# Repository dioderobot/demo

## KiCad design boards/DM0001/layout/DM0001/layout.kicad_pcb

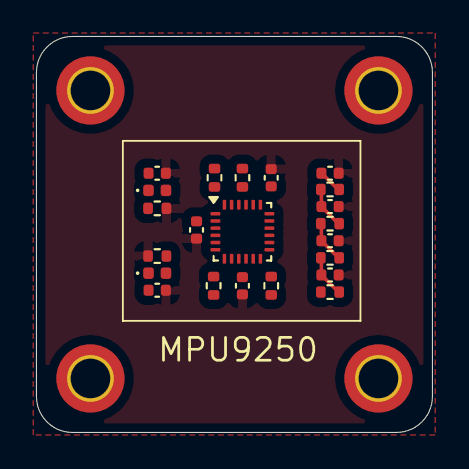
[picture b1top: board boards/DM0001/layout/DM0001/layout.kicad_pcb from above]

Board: 4 copper layers, 22.0 x 22.0 mm, 26 parts (0 on the bottom side), 13 nets.

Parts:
C1, C2, C3, C9: 100nF; C_0402_1005Metric
C4, C5, C6, C7, C8: 10nF; C_0402_1005Metric
D1, D2: LED GREEN; LED_0402_1005Metric
H1, H2, H3, H4: M2 DIN965 TopBottom; MountingHole_2.2mm_M2_DIN965_Pad_TopBottom
R1, R10: 1k; R_0402_1005Metric
R2, R3: 4.7k; R_0402_1005Metric
R4, R5: 10k; R_0402_1005Metric
R6, R7, R8, R9: 820; R_0402_1005Metric
U1: ?; InvenSense_QFN-24_3x3mm_P0.4mm

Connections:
Imu.LED.L: D1.1, R1.1
Imu.MPU9250.CS_PULLUP: R4.1, U1.22
Imu.MPU9250.REGOUT: C2.1, U1.10
Imu.NC: R3.1, U1.21
Imu.NC_2: R2.1, U1.7
LowPassFilter.STAGE1_OUT: C5.1, R6.2, R7.1
LowPassFilter.STAGE2_OUT: C6.1, R7.2, R8.1
LowPassFilter.STAGE3_OUT: C7.1, R8.2, R9.1
MCU_IN: C8.1, R9.2
PowerLed.L: D2.1, R10.1
SENSOR_OUT: R5.1, R6.1, U1.12
gnd_GND: C1.2, C2.2, C3.2, C4.2, C5.2, C6.2, C7.2, C8.2, C9.2, R1.2, R10.2, U1.9, U1.18, U1.20
vcc_VCC: C1.1, C3.1, C4.1, C9.1, D1.2, D2.2, R2.2, R3.2, R4.2, R5.2, U1.1, U1.8, U1.13

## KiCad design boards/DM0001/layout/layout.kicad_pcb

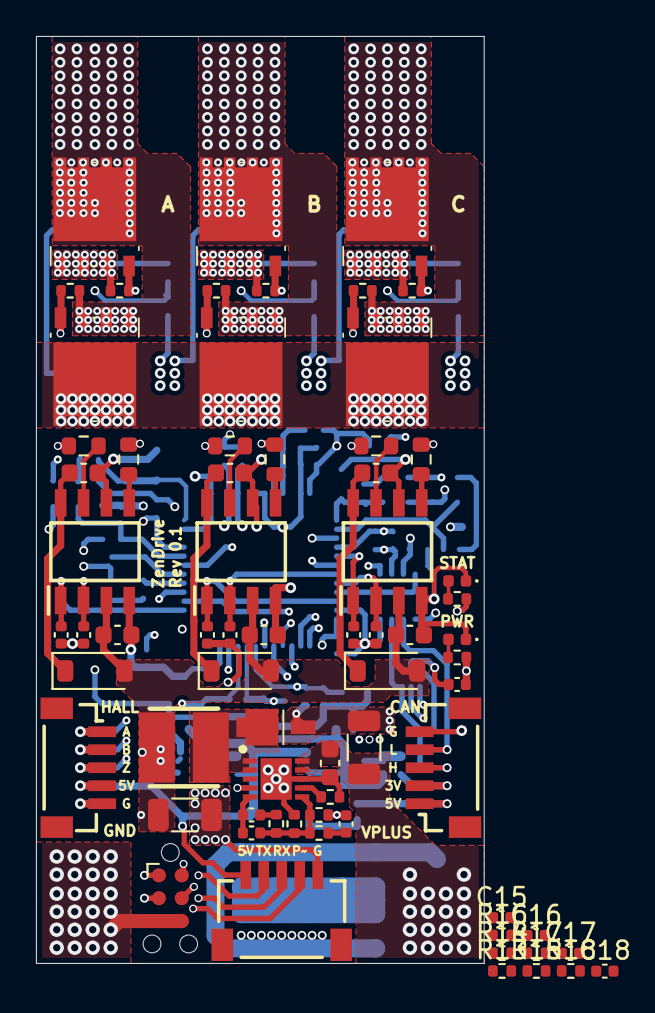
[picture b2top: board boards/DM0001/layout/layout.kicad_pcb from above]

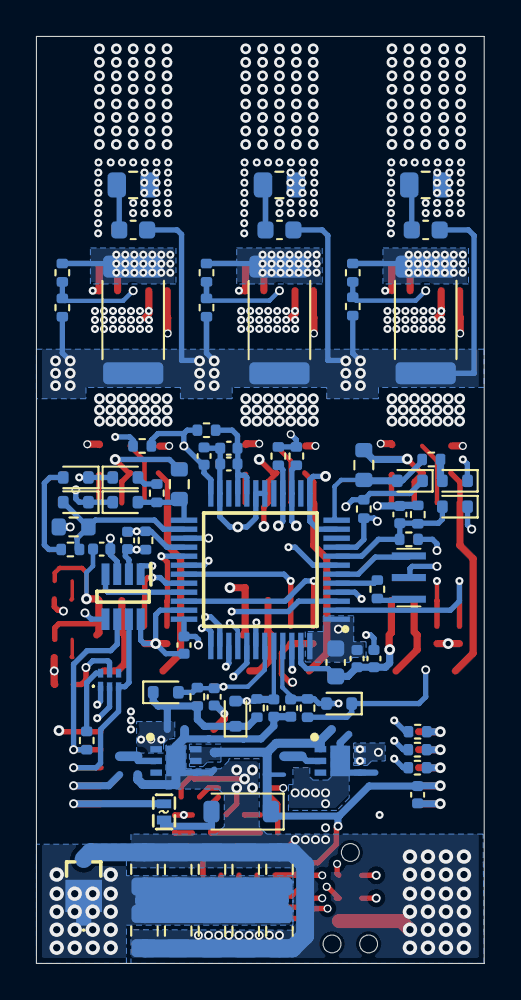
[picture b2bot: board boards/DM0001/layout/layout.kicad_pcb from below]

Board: 6 copper layers, 24.9 x 51.5 mm, 149 parts (80 on the bottom side), 85 nets.

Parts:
C1: CL31B106KAHNNNE; C_1206_3216Metric
C2: GCM188R71H224KA64D; C_0603_1608Metric
C3: CL31A226MOCLNNC; C_1206_3216Metric
C4: GCM1555C1H300FA16D; C_0402_1005Metric
C5: GRM155R71H472KA01D; C_0402_1005Metric
C6: CL05B392KB5NNNC; C_0402_1005Metric
C7: CL05B103KB5NNNC; C_0402_1005Metric
C8, C9, C10, C14, C44, C45, C47, C50: GCM155R71H104KE02D; C_0402_1005Metric
C11, C12, C13: GCM1555C1H100FA16D; C_0402_1005Metric
C15, C17: 1uF 10% 25V; C_0402_1005Metric
C16, C18: 2.2uF 10% 16V; C_0402_1005Metric
C19, C24, C29: GRM1885C1H102JA01D; C_0603_1608Metric
C20, C25, C30: GCM188R71E105KA64D; C_0603_1608Metric
C21, C22, C26, C27, C31, C32: GCM1555C1H101FA16D; C_0402_1005Metric
C23, C28, C33: CL10A474KA8NNNC; C_0603_1608Metric
C34, C35, C36, C37, C38, C39, C40, C41, C42, C43: C2012X5R1V226M125AC; C_0805_2012Metric
C46: GRM188Z71C475KE21D; C_0603_1608Metric
C48: CL05A105KP5NNNC; C_0402_1005Metric
C49: GRM1555CYA103GE01D; C_0402_1005Metric
D1: STPS1L40M
D2: 1N5817W; D_SOD-123
D3, D4, D5, D6, D7, D8, D10, D11, D13, D14: BAT30KFILM; D_SOD-523
D9, D12, D15: STPS0560Z; D_SOD-123
D16: VLMG1500-GS08; LED_0402_1005Metric
D17: VLMS1500-GS08; LED_0402_1005Metric
F1: 0435.250KRS; F0402
FB1: MMZ1005S601CT000; R_0402_1005Metric
IC1: TCAN330DCNT; SOT65P280X145-8N
IC2, IC3: LDFPVR; SON65P200X200X100-7N-D
IC4, IC5, IC6: L6387ED; SOIC127P600X175-8N
IC7: STM32G431C8T6; QFP50P900X900X160-48N
J1, J2: BM05B-SRSS-TB(LF)(SN); BM05BSRSSTB
J3: SM05B-SRSS-TB(LF)(SN); SM05BSRSSTB
J4: ?; Tag-Connect_TC2030-IDC-NL_2x03_P1.27mm_Vertical
L1: ?; IND-SMD_L3.9-W3.9
PS1: L7986TR; SON50P300X300X100-11N-D
Q1, Q2, Q3, Q4, Q5, Q6: STL180N6F7; STL140N6F7
R1, R45: ERJ-2RKF4701X; R_0402_1005Metric
R2: ERJ-2RKF3000X; R_0402_1005Metric
R3: ERJ-2RKF3482X; R_0402_1005Metric
R4: ERJ-2RKF8201X; R_0402_1005Metric
R5: ERJ-2RKF62R0X; R_0402_1005Metric
R6: ERJ-2RKF1200X; R_0402_1005Metric
R7, R8, R9, R10, R11, R12, R13, R16, R21, R23, R29, R31, R37, R39: ERJ-2RKF1002X; R_0402_1005Metric
R14: ERJ-2RKF3092X; R_0402_1005Metric
R15, R18: ERJ-2RKF4702X; R_0402_1005Metric
R17: ERJ-2RKF5232X; R_0402_1005Metric
R19, R27, R35, R49, R50, R51: ERJ-2RKF2201X; R_0402_1005Metric
R20, R22, R28, R30, R36, R38: ERJ-3EKF33R0V; R_0603_1608Metric
R24, R32, R40: ERJ-3EKF1002V; R_0603_1608Metric
R25, R33, R41: RC0805JR-071RL; R_0805_2012Metric
R26, R34, R42: CSNL2512FT3L00; R_2512_6332Metric
R43, R44: ERJ-2RKF1001X; R_0402_1005Metric
R46: ERJ-2RKF1802X; R_0402_1005Metric
R47: ERJ-2RKF1693X; R_0402_1005Metric
R48: ERJ-2RKF2200X; R_0402_1005Metric
R52, R53, R54: ERJ-2RKF2202X; R_0402_1005Metric
R55, R56, R57: ERJ-2RKF1501X; R_0402_1005Metric
S1: FSA5157L6X
TH1: NTCG103JF103FT1; R_0402_1005Metric
Y1: CSTNE8M00GH5C000R0; CSTNE12M0GH5L000R0
Z1: SMM4F26A-TR; SMM4F15ATR

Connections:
A_PLUS_H1: C11.1, D4.2, IC7.43, R7.2, R8.2
BEMF1: D8.2, IC7.12, R19.2, R24.2
BEMF2: D11.2, IC7.26, R27.2, R32.2
BEMF3: D14.2, IC7.25, R35.2, R40.2
B_PLUS_H2: C12.1, D5.2, IC7.44, R9.2, R10.2
Buck.COMP: C4.1, C5.2, PS1.5
Buck.FB: C4.2, PS1.6, R1.2, R2.1, R4.1, R5.2
Buck.FSW: PS1.7, R3.1
Buck.OUT: D1.1, D1.2, L1.1, PS1.1, PS1.2
Buck.R_SMALL_SIGNAL: C5.1, R4.2
Buck.R_SMALL_SIGNAL_2: C6.2, R5.1
CAN_RX: IC1.4, IC7.33
CAN_SHDN: IC1.5, IC7.27
CAN_TERM: IC7.3, S1.1
CAN_TX: IC1.1, IC7.46
CURR_FDBK1_OPAMP+: IC7.9, R49.1, R52.2, R55.1
CURR_FDBK2_OPAMP+: IC7.15, R50.1, R53.2, R56.1
CURR_FDBK3_OPAMP+: IC7.16, R51.1, R54.2, R57.1
Can_Interface.CAN_H: IC1.7, J1.3, S1.3
Can_Interface.CAN_L: IC1.6, J1.4, R6.1
Can_Interface.FUSE: D2.2, F1.1
Can_Interface.JST_5V: F1.2, J1.1
Can_Interface.S1: R6.2, S1.6
GND: C1.2, C2.2, C3.2, C7.2, C8.2, C9.2, C10.2, C11.2, C12.2, C13.2, C14.2, C15.2, C16.2, C17.2, C18.2, C19.2, C21.2, C22.2, C23.2, C24.2, C26.2, C27.2, C28.2, C29.2, C31.2, C32.2, C33.2, C34.2, C35.2, C36.2, C37.2, C38.2, C39.2, C40.2, C41.2, C42.2, C43.2, C44.2, C45.2, C46.2, C47.2, C48.2, C49.2, C50.2, D1.3, D16.1, D17.1, IC1.2, IC1.8, IC2.4, IC2.7, IC3.4, IC3.7, IC4.4, IC5.4, IC6.4, IC7.11, IC7.13, IC7.18, IC7.19, IC7.23, IC7.35, IC7.47, J1.5, J2.5, J3.5, J4.5, J4.6, PS1.8, PS1.11, R2.2, R3.2, R13.2, R16.2, R26.2, R34.2, R42.2, R45.2, R46.2, R49.2, R50.2, R51.2, S1.5, Y1.2, Z1.2
GPIO_BEMF: D7.1, D10.1, D13.1, IC7.42
HallEncoder.A_PLUS_H1_IN: J2.1, R8.1
HallEncoder.B_PLUS_H2_IN: J2.2, R10.1
HallEncoder.Z_PLUS_H3_IN: J2.3, R12.1
Ldo_3V3.LDFPVR.NC_LDFPVR_PG: IC2.3, R15.1
Ldo_3V3._ADJ: IC2.2, R13.1, R14.2
Ldo_5V.LDFPVR.NC_LDFPVR_PG: IC3.3, R18.1
Ldo_5V._ADJ: IC3.2, R16.1, R17.2
NRST: C50.1, IC7.7, J4.3
PHASE_A: C20.2, IC4.6, Q1.1, Q1.2, Q1.3, Q2.5, Q2.6, Q2.7, Q2.8, Q2.9, R21.2, R24.1, R25.1
PHASE_B: C25.2, IC5.6, Q3.1, Q3.2, Q3.3, Q4.5, Q4.6, Q4.7, Q4.8, Q4.9, R29.2, R32.1, R33.1
PHASE_C: C30.2, IC6.6, Q5.1, Q5.2, Q5.3, Q6.5, Q6.6, Q6.7, Q6.8, Q6.9, R37.2, R40.1, R41.1
PWM: IC7.39, J3.4
PhaseDriverA.D_BEMF: D7.2, R19.1
PhaseDriverA.HI_GATE: Q1.4, R20.2, R21.1
PhaseDriverA.HVG: IC4.7, R20.1
PhaseDriverA.LO_GATE: Q2.4, R22.2, R23.1
PhaseDriverA.LVG: IC4.5, R22.1
PhaseDriverA.RC_NODE: C19.1, R25.2
PhaseDriverA.U1.BOOT: C20.1, D9.1, IC4.8
PhaseDriverB.D_BEMF: D10.2, R27.1
PhaseDriverB.HI_GATE: Q3.4, R28.2, R29.1
PhaseDriverB.HVG: IC5.7, R28.1
PhaseDriverB.LO_GATE: Q4.4, R30.2, R31.1
PhaseDriverB.LVG: IC5.5, R30.1
PhaseDriverB.RC_NODE: C24.1, R33.2
PhaseDriverB.U1.BOOT: C25.1, D12.1, IC5.8
PhaseDriverC.D_BEMF: D13.2, R35.1
PhaseDriverC.HI_GATE: Q5.4, R36.2, R37.1
PhaseDriverC.HVG: IC6.7, R36.1
PhaseDriverC.LO_GATE: Q6.4, R38.2, R39.1
PhaseDriverC.LVG: IC6.5, R38.1
PhaseDriverC.RC_NODE: C29.1, R41.2
PhaseDriverC.U1.BOOT: C30.1, D15.1, IC6.8
R_POWER_LED: D16.2, R43.2
R_STATUS_LED: D17.2, R44.2
STATUS: IC7.4, R44.1
STM32G431C8T6.R_XIN: IC7.5, R48.2
STM32G431C8T6.VDDA: C48.1, C49.1, FB1.2, IC7.20, IC7.21
STM32G431C8T6.XIN: R48.1, Y1.1
STM32G431C8T6.XOUT: IC7.6, Y1.3
SWD_SWCLK: IC7.38, J4.4
SWD_SWDIO: IC7.37, J4.2
TEMP_FEEDBACK: C7.1, IC7.28, R45.1, TH1.2
TIM1_CH1: C21.1, IC4.2, IC7.30
TIM1_CH1N: C22.1, IC4.1, IC7.2
TIM1_CH2: C26.1, IC5.2, IC7.31
TIM1_CH2N: C27.1, IC5.1, IC7.34
TIM1_CH3: C31.1, IC6.2, IC7.32
TIM1_CH3N: C32.1, IC6.1, IC7.29
UART2_RX: IC7.41, J3.3
UART2_TX: IC7.40, J3.2
V3V3: C9.1, C10.1, C16.1, C44.1, C45.1, C46.1, C47.1, D3.1, D4.1, D5.1, D6.1, D8.1, D11.1, D14.1, FB1.1, IC1.3, IC2.1, IC7.1, IC7.24, IC7.36, IC7.48, J1.2, J4.1, R7.1, R9.1, R11.1, R14.1, R43.1, R52.1, R53.1, R54.1, S1.2, TH1.1
V5V: C14.1, C15.1, C18.1, D2.1, IC2.5, IC2.6, IC3.1, J2.4, J3.1, R15.2, R17.1
V10V: C3.1, C6.1, C17.1, C23.1, C28.1, C33.1, D9.2, D12.2, D15.2, IC3.5, IC3.6, IC4.3, IC5.3, IC6.3, L1.2, R1.1, R18.2
VBUS: C8.1, D3.2, IC7.8, R46.1, R47.2
VPLUS: C1.1, C2.1, C34.1, C35.1, C36.1, C37.1, C38.1, C39.1, C40.1, C41.1, C42.1, C43.1, PS1.4, PS1.9, PS1.10, Q1.5, Q1.6, Q1.7, Q1.8, Q1.9, Q3.5, Q3.6, Q3.7, Q3.8, Q3.9, Q5.5, Q5.6, Q5.7, Q5.8, Q5.9, R47.1, Z1.1, Z1.3
VSHUNTP_A: Q2.1, Q2.2, Q2.3, R23.2, R26.1, R55.2
VSHUNTP_B: Q4.1, Q4.2, Q4.3, R31.2, R34.1, R56.2
VSHUNTP_C: Q6.1, Q6.2, Q6.3, R39.2, R42.1, R57.2
Z_PLUS_H3: C13.1, D6.2, IC7.45, R11.2, R12.2

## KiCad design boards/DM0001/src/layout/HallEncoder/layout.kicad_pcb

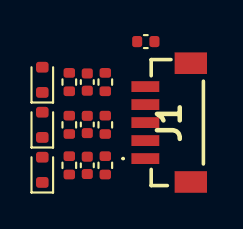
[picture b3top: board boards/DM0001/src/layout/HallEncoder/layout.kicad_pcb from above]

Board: 2 copper layers, 14 parts (0 on the bottom side), 9 nets, no tracks yet.

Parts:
C1, C2, C3: GCM1555C1H100FA16D; C_0402_1005Metric
C4: GCM155R71H104KE02D; C_0402_1005Metric
D1, D2, D3: BAT30KFILM; D_SOD-523
J1: BM05B-SRSS-TB(LF)(SN); BM05BSRSSTB
R1, R2, R3, R4, R5, R6: ERJ-2RKF1002X; R_0402_1005Metric

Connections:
A_PLUS_H1_IN: J1.1, R2.1
A_PLUS_H1_OUT: C1.1, D1.2, R1.2, R2.2
B_PLUS_H2_IN: J1.2, R4.1
B_PLUS_H2_OUT: C2.1, D2.2, R3.2, R4.2
GND: C1.2, C2.2, C3.2, C4.2, J1.5
V3V3: D1.1, D2.1, D3.1, R1.1, R3.1, R5.1
V5V: C4.1, J1.4
Z_PLUS_H3_IN: J1.3, R6.1
Z_PLUS_H3_OUT: C3.1, D3.2, R5.2, R6.2

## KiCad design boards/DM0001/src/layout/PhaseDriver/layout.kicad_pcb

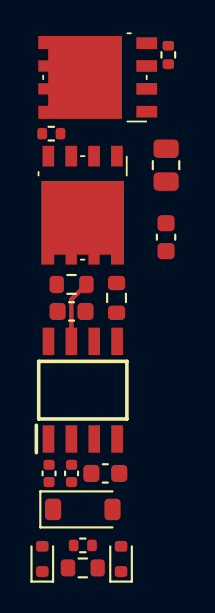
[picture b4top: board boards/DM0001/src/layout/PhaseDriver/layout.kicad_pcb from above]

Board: 2 copper layers, 19 parts (1 on the bottom side), 15 nets.

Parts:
C1: 1nF 100V; C_0603_1608Metric
C2: 1uF 25V; C_0603_1608Metric
C3, C4: 100pF 10V; C_0402_1005Metric
C5: 470nF 16V; C_0603_1608Metric
D1, D2: BAT30KFILM; D_SOD-523
D3: STPS0560Z; D_SOD-123
R1: 2.2k; R_0402_1005Metric
R2, R4: 33; R_0603_1608Metric
R3, R5: 10k; R_0402_1005Metric
R6: 10k; R_0603_1608Metric
R7: 1; R_0805_2012Metric
R8: 3m 1%; R_2512_6332Metric
U1, U2: STL180N6F7; STL140N6F7
U3: L6387ED; SOIC127P600X175-8N

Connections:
BEMF: D2.2, R1.2, R6.2
D_BEMF: D1.2, R1.1
GND: C1.2, C3.2, C4.2, C5.2, R8.2, U3.4
HI_GATE: R2.2, R3.1, U1.4
HVG: R2.1, U3.7
LO_GATE: R4.2, R5.1, U2.4
LVG: R4.1, U3.5
PHASEOUT: C2.2, R3.2, R6.1, R7.1, U1.1, U1.2, U1.3, U2.5, U2.6, U2.7, U2.8, U2.9, U3.6
RC_NODE: C1.1, R7.2
TIM_CHN: C4.1, U3.1
TIM_CHP: C3.1, U3.2
U1.BOOT: C2.1, D3.1, U3.8
VCC: C5.1, D3.2, U3.3
VPLUS: U1.5, U1.6, U1.7, U1.8, U1.9
VSHUNTP: R5.2, R8.1, U2.1, U2.2, U2.3

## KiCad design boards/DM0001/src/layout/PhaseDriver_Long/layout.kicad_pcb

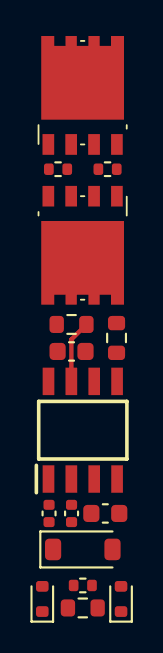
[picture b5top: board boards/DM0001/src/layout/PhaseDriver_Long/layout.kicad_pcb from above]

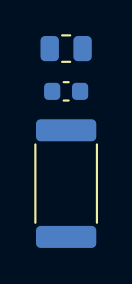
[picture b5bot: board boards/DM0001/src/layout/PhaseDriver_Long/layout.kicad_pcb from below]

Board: 2 copper layers, 19 parts (3 on the bottom side), 15 nets.

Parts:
C1: GRM1885C1H102JA01D; C_0603_1608Metric
C2: GCM188R71E105KA64D; C_0603_1608Metric
C3, C4: GCM1555C1H101FA16D; C_0402_1005Metric
C5: CL10A474KA8NNNC; C_0603_1608Metric
D1, D2: BAT30KFILM; D_SOD-523
D3: STPS0560Z; D_SOD-123
IC1: L6387ED; SOIC127P600X175-8N
Q1, Q2: STL180N6F7; STL140N6F7
R1: ERJ-2RKF2201X; R_0402_1005Metric
R2, R4: ERJ-3EKF33R0V; R_0603_1608Metric
R3, R5: ERJ-2RKF1002X; R_0402_1005Metric
R6: ERJ-3EKF1002V; R_0603_1608Metric
R7: RC0805JR-071RL; R_0805_2012Metric
R8: CSNL2512FT3L00; R_2512_6332Metric

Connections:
BEMF: D2.2, R1.2, R6.2
D_BEMF: D1.2, R1.1
GND: C1.2, C3.2, C4.2, C5.2, IC1.4, R8.2
HI_GATE: Q1.4, R2.2, R3.1
HVG: IC1.7, R2.1
LO_GATE: Q2.4, R4.2, R5.1
LVG: IC1.5, R4.1
PHASEOUT: C2.2, IC1.6, Q1.1, Q1.2, Q1.3, Q2.5, Q2.6, Q2.7, Q2.8, Q2.9, R3.2, R6.1, R7.1
RC_NODE: C1.1, R7.2
TIM_CHN: C4.1, IC1.1
TIM_CHP: C3.1, IC1.2
U1.BOOT: C2.1, D3.1, IC1.8
VCC: C5.1, D3.2, IC1.3
VPLUS: Q1.5, Q1.6, Q1.7, Q1.8, Q1.9
VSHUNTP: Q2.1, Q2.2, Q2.3, R5.2, R8.1

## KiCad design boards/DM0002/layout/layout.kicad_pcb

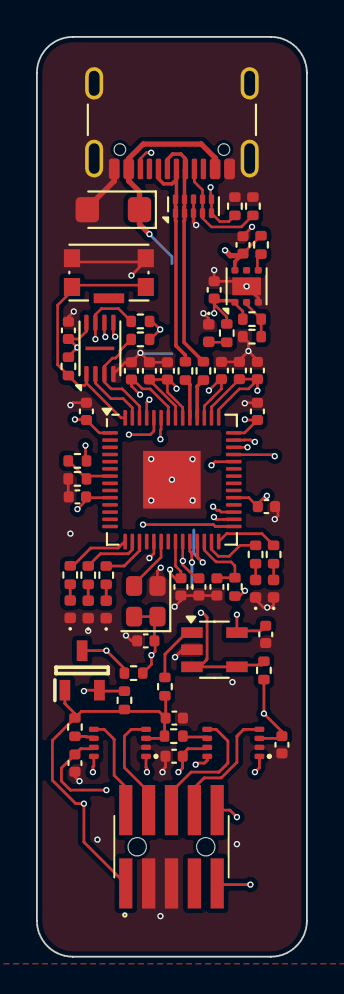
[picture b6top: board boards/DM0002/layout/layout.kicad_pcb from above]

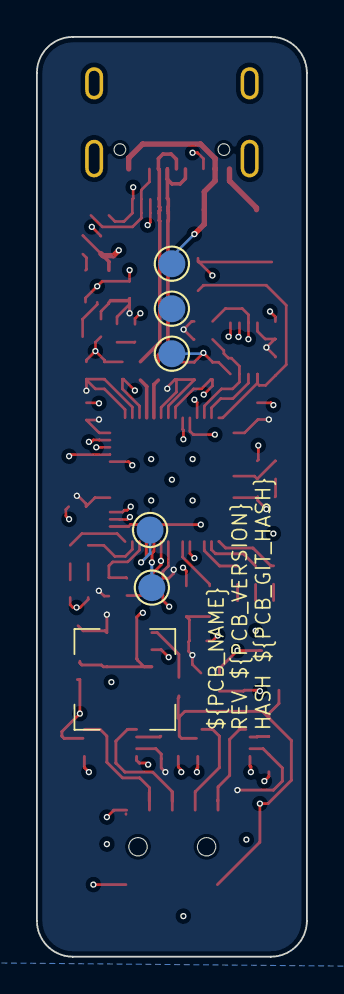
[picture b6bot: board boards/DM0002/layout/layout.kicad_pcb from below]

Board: 4 copper layers, 15.0 x 51.1 mm, 73 parts (6 on the bottom side), 50 nets.

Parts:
C1, C2, C3, C4, C7, C8, C9, C10, C11, C12, C13, C14, C15, C16, C17, C20, C21, C22: GCM155R71H104KE02D; C_0402_1005Metric
C5, C6, C18, C19: GRM155Z71A105KE01D; C_0402_1005Metric
D1: VLMB1500-GS08; LED_0402_1005Metric
D2: VLMG1500-GS08; LED_0402_1005Metric
D3, D4, D5: VLMO1500-GS08; LED_0402_1005Metric
D6: VLMS1500-GS08; LED_0402_1005Metric
D7: SMF5V0A-E3-08; D_SMF
D8: TPD4E05U06QDQARQ1; USON-10_2.5x1.0mm_P0.5mm
J1: FTSH-105-01-L-DV-K-A-P-TR
J2: USB4105-GF-A; USB_C_Receptacle_GCT_USB4105-xx-A_16P_TopMnt_Horizontal
Q1: BSS138-7-F; SOT96P240X115-3N
R1, R3, R10, R11, R12, R13, R17, R18, R19, R24, R25: ERJ-2RKF1002X; R_0402_1005Metric
R2, R21: ERJ-2RKF4702X; R_0402_1005Metric
R4: ERJ-2RKF1100X; R_0402_1005Metric
R5, R9: ERJ-2RKF1500X; R_0402_1005Metric
R6, R7, R8: ERJ-2RKF2610X; R_0402_1005Metric
R14, R15: ERJ-2RKF27R0X; R_0402_1005Metric
R16: ERJ-2GE0R00X; R_0402_1005Metric
R20: ERJ-2RKF3302X; R_0402_1005Metric
R22, R23: ERJ-2RKF5101X; R_0402_1005Metric
SW1: KMR231G LFS; SW_Push_1P1T-SH_NO_CK_KMR2xxG
TP1: ?; logo
TP2, TP3, TP4, TP5, TP6: ?; TestPoint_Pad_D1.5mm
U1: TLV75801PDRVR; WSON-6-1EP_2x2mm_P0.65mm_EP1x1.6mm
U2: W25Q16JVUXIQ; Winbond_USON-8-1EP_3x2mm_P0.5mm_EP0.2x1.6mm
U3: RP2040; QFN-56-1EP_7x7mm_P0.4mm_EP3.2x3.2mm
U4: SG-210STF 12.0000ML0; Oscillator_SMD_SeikoEpson_SG210-4Pin_2.5x2.0mm
U5, U6: TXB0102DCUR; VSSOP-8_2.3x2mm_P0.5mm
U7: TLV9001IDBVR; SOT95P280X145-5N
V1: ?; version-footprint

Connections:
GND: C1.2, C2.2, C3.2, C4.2, C5.2, C6.2, C7.2, C8.2, C9.2, C10.2, C11.2, C12.2, C13.2, C14.2, C15.2, C16.2, C17.2, C18.2, C19.2, C20.2, C21.2, C22.2, D1.1, D2.1, D3.1, D4.1, D5.1, D6.1, D7.2, D8.3, D8.8, J1.3, J1.5, J2.A1, J2.A12, J2.B1, J2.B12, J2.S1, R3.2, R21.2, R22.2, R23.2, SW1.2, TP5.1, U1.3, U1.7, U2.4, U3.19, U3.57, U4.2, U5.2, U6.2, U7.2
LDO_3V3.EN: R1.2, U1.4
LDO_3V3.LDO_FB: R2.2, R3.1, U1.2
LED_B: R4.1, U3.28
LED_B.LED_R_NET: D1.2, R4.2
LED_G: R5.1, U3.27
LED_G.LED_R_NET: D2.2, R5.2
LED_O1: R6.1, U3.17
LED_O1.LED_R_NET: D3.2, R6.2
LED_O2: R7.1, U3.16
LED_O2.LED_R_NET: D4.2, R7.2
LED_O3: R8.1, U3.15
LED_O3.LED_R_NET: D5.2, R8.2
LED_PWR.LED_R_NET: D6.2, R9.2
MCU.QSPI_CLK: U2.6, U3.52
MCU.QSPI_CS: R10.1, SW1.1, U2.1, U3.56
MCU.QSPI_IO0: U2.5, U3.53
MCU.QSPI_IO1: U2.2, U3.55
MCU.QSPI_IO2: R11.2, U2.3, U3.54
MCU.QSPI_IO3: R12.2, U2.7, U3.51
MCU.RUN: C16.1, R13.2, U3.26
MCU.SWD_SWCLK: TP2.1, U3.24
MCU.SWD_SWDIO: TP3.1, U3.25
MCU.USB_MCU_D_N: R14.1, U3.46
MCU.USB_MCU_D_P: R15.1, U3.47
MCU.VDD_1V1: C8.1, C9.1, C19.1, U3.23, U3.45, U3.50
MCU.XO_XIN: U3.20, U4.3
MCU_SWCLK: U3.30, U5.1
MCU_SWDIO: U3.31, U5.8
MCU_UART_RX: U3.40, U6.8
MCU_UART_TX: U3.41, U6.1
SWD_LS_OE: R17.2, U5.6
SWD_SWCLK: J1.4, U5.4
SWD_SWDIO: J1.2, U5.5
TARGET_GND_DETECT: J1.9, U3.39
TARGET_RESET: J1.10, Q1.2, R25.2
TARGET_RESET_TO_MCU: Q1.3, R24.2, U3.29
TARGET_UART_RX: J1.6, U6.5
TARGET_UART_TX: J1.8, U6.4
TARGET_VDDIO: C1.1, C3.1, J1.1, Q1.1, R16.1, R17.1, R18.1, R19.1, R25.1, U5.3, U6.3
TARGET_V_SENSE_BUFFER: R16.2, U3.38, U7.3, U7.4
TARGET_V_SENSE_R: R19.2, U7.1
UART_LS_OE: R18.2, U6.6
USB_C.CC1: D8.4, D8.7, J2.A5, R22.1
USB_C.CC2: D8.5, D8.6, J2.B5, R23.1
USB_D_N: D8.2, D8.9, J2.A7, J2.B7, R14.2
USB_D_P: D8.1, D8.10, J2.A6, J2.B6, R15.2
VBUS_5V0: C5.1, D7.1, J2.A4, J2.A9, J2.B4, J2.B9, R1.1, R20.1, TP6.1, U1.6
VBUS_DET: R20.2, R21.1, U3.7
VDD_3V3: C2.1, C4.1, C6.1, C7.1, C10.1, C11.1, C12.1, C13.1, C14.1, C15.1, C17.1, C18.1, C20.1, C21.1, C22.1, R2.1, R9.1, R10.2, R11.1, R12.1, R13.1, R24.1, TP4.1, U1.1, U2.8, U3.1, U3.10, U3.22, U3.33, U3.42, U3.43, U3.44, U3.48, U3.49, U4.1, U4.4, U5.7, U6.7, U7.5

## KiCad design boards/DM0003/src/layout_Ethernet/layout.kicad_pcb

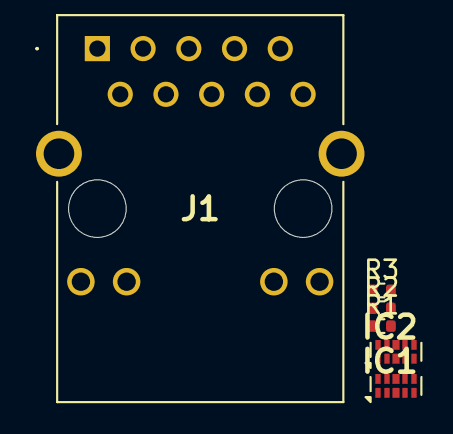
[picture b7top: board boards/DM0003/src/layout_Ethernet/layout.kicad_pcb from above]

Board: 2 copper layers, 6 parts (0 on the bottom side), 13 nets, no tracks yet.

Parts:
IC1, IC2: TPD4EUSB30DQAR; DQA_R-PUSON-N10_
J1: CRJ009-ML4-TH; CRJ009ML4TH
R1: ERJ-2GE0R00X; R_0402_1005Metric
R2, R3: ERJ-2RKF4700X; R_0402_1005Metric

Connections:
3V3PI: J1.11, J1.13
ETH_C_TR0_N: IC1.2, IC1.9, J1.2
ETH_C_TR0_P: IC1.1, IC1.10, J1.1
ETH_C_TR1_N: IC1.5, IC1.6, J1.4
ETH_C_TR1_P: IC1.4, IC1.7, J1.3
ETH_C_TR2_N: IC2.2, IC2.9, J1.8
ETH_C_TR2_P: IC2.1, IC2.10, J1.7
ETH_C_TR3_N: IC2.5, IC2.6, J1.10
ETH_C_TR3_P: IC2.4, IC2.7, J1.9
GND: IC1.3, IC1.8, IC2.3, IC2.8, R1.2
K_GREEN: J1.14, R3.1
K_YELLOW: J1.12, R2.1
MP: J1.MH1, J1.MH2, R1.1
